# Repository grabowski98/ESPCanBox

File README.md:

<!-- Project name: "project_name" in project.json. tools/set_project_name.py --apply rewrites the title line ("# ...") under the logo. The logo is a drawing: no tool rewrites it (docs/en/contributing/brand.md). -->

# ESPCanBox

An open ESP32-S3 device that sits between a car's CAN bus and an Android radio and can replace
the aftermarket CAN interface box sold with the radio.

English | [Polski](README.pl.md) | [Deutsch](README.de.md) | [Español](README.es.md) | [Русский](README.ru.md) | [Українська](README.uk.md)

> [!WARNING]
> **Hobby project, provided AS IS, without any warranty.** You use it at your own risk, on your
> own car.
>
> - By default the device **only listens** to the car bus. Transmitting needs a separate build
>   (`decoder_tx_wifi`) and arming by hand. Read [Transmitting on the CAN bus](docs/en/safety/transmit.md)
>   before you build it.
> - Do not use it for anything that affects safety (brakes, steering, airbags, lights required by
>   law). It is not designed or tested for that.
> - The firmware and the board were developed and measured on **one** car with **one** radio.
>   Every other car is untested.
> - This project is not affiliated with, endorsed by or connected to Peugeot, Stellantis,
>   Simple Soft, Raise, Junsun or FYT. Their names are used only to say what was tested.

## Who it is for

Hobbyists who can solder a small board, use a multimeter and build firmware with PlatformIO
(the guides show every command). What you get depends on your car and radio:

- **Peugeot 508 SW (PSA AEE2010) with an Android radio that speaks the "XP" protocol:** the
  device can replace the CAN box: buttons, parking sensors, trip computer and radio power.
- **Any other car:** listen and record the CAN bus (build `listen_generic_wifi`), then decode it
  and write your own car profile with the [Make it yours](docs/en/make-it-yours/porting-checklist.md)
  guides. Nothing is sent to the radio until your profile exists.
- **Any other radio:** "XP" is the only radio protocol so far. Another radio needs a new
  protocol in the firmware ([Radio mapping](docs/en/make-it-yours/radio-mapping.md)).

## What it does

- **Listens to the car's CAN bus** and never transmits in the default builds. Only the separate
  build `decoder_tx_wifi` contains transmit code; a script checks this after every build.
- **Beeps for the parking sensors** from its own small speaker.
- **Talks to the radio** in decoder mode, like the CAN box did: steering wheel and centre panel
  buttons, parking sensor display, trip computer, outside temperature, climate state, doors and
  vehicle settings.
- **Switches three 12 V lines** for the radio in decoder mode: ACC (radio power), illumination,
  reverse.
- **Web panel** over its own Wi-Fi network: status, live CAN frames, console, recording,
  firmware update. Panel languages: English, Polish, German, Spanish, Russian, Ukrainian (the
  last four are machine translations that need review).
- **USB console** with a fixed line format that tools can read
  (see [Console](docs/en/reference/console.md)).
- **Car profiles and radio protocols chosen at build time:** `psa_aee2010` (reference car) or
  `generic` (any car, listen only); radio protocol `XP` or `NONE`. A template for your own car is
  in `firmware/lib/car_example` (see [Write a profile](docs/en/make-it-yours/write-a-profile.md)).
- **Tests on your computer** of all the logic, on recordings from the car, without hardware
  (see [Host tests](docs/en/testing/host-tests.md)).
- **Optional transmit build** (`decoder_tx_wifi`): by default it can send only one frame, the
  vehicle settings request `15B` (checked by ID and length only), and only after you arm it.
  Two more trial frames exist only in an experimental build. Climate control from the radio
  this way did **not** work. Details: [Transmitting on the CAN bus](docs/en/safety/transmit.md).

Not done or not known: deep sleep when the bus is silent is written but not tested on the
hardware. The firmware in this repository was reorganised from the version that runs in the
reference car; it compiles and passes the host tests, but this tree has **not yet been
bench-tested** on a device.

## Supported cars

| Car | Firmware profile | Status |
|---|---|---|
| Peugeot 508 SW, 2015 (PSA AEE2010) | `psa_aee2010` | measured on one car |
| any car | `generic` (build `listen_generic_wifi`) | listen-only: records frames, sends nothing to the radio, 12 V outputs off |

On the reference car the bus at the radio runs at 125 kbit/s (measured). Its voltages look like
low-speed fault-tolerant CAN (CANH about 0.65 V, CANL about 4.5 V average with ignition on); this
is not yet confirmed with an oscilloscope. Details: `vehicles/peugeot-508-sw-2015/README.md` and
`vehicles/SUPPORTED.md`.

## Supported radios

| Radio protocol | Firmware | Status |
|---|---|---|
| "XP" (Simple Soft CAN box protocol, Android radio on the FYT platform, CAN profile "XP Simple Soft -> Peugeot 508 -> Type 2") | `-DRADIO_PROTOCOL=XP` | measured on one radio (UART recordings of the box and the radio) |
| no radio | `-DRADIO_PROTOCOL=NONE` | nothing is sent on the UART |

Protocol description, only from recordings: `radios/xp-simple-soft/protocol.md`.

## Quick start

This gets the device running on your desk, with no car. You need an ESP32-S3 board with 16 MB
flash and 8 MB PSRAM (N16R8) and a USB cable. Full guide: [Quick start](docs/en/quick-start/flash.md).

1. **Read [Safety](docs/en/getting-started/safety.md).** Nothing goes into the car before that.
2. **Install the tools.** Install [uv](https://docs.astral.sh/uv/); it runs PlatformIO without a
   separate install. Git for Windows (Git Bash) is not needed to flash: it is needed for the
   tests on your computer and for the pages of "Make it yours" (your own car or radio).
3. **Build and flash the listen-only build with the web panel.** Type this in the top folder of
   the repository (on Windows in PowerShell):

   ```
   uvx platformio run -d firmware -e listen_wifi -t upload
   ```

4. **Open the USB console** (115200 baud), for example
   `uvx platformio device monitor -d firmware`. Your typing is not shown; press Enter after each
   command. Type `ver`, then `stat`, then `wifi` (network name) and `wifi showpass` (password).
   Keep the password out of any log you share.
5. **Open the panel.** Connect a phone or a laptop to the Wi-Fi network of the device (its name
   is printed by `wifi`), open `http://10.50.8.1` and log in with that password. Pick your
   language on the login screen.

For a car other than the reference car, use `listen_generic_wifi` later.

Next: [Bench test](docs/en/quick-start/bench-test.md), then
[Make it yours](docs/en/make-it-yours/porting-checklist.md) for another car, or
[Install in the car](docs/en/install-in-car/checklist.md) for the reference car.

No board yet? The mock device runs the panel on your computer with a recording:
`python -I firmware/tools/mock_device.py firmware/test_data/captures/can_20261111_191045.log`
(on Linux and macOS: `python3`; see [First boot](docs/en/quick-start/first-boot.md)).

## Documentation

- [Overview](docs/en/index.md) and [How it works](docs/en/getting-started/how-it-works.md)
- [Safety](docs/en/getting-started/safety.md), [Transmitting on the CAN bus](docs/en/safety/transmit.md),
  [Security model](docs/en/safety/security.md)
- [Hardware](docs/en/hardware/overview.md): prototype board, parts list, enclosure, wiring
- [Make it yours](docs/en/make-it-yours/porting-checklist.md): record, decode and add your own car
- [Reference](docs/en/reference/architecture.md): protocol, console, panel API, pins
- [Troubleshooting](docs/en/troubleshooting/index.md) and [FAQ](docs/en/troubleshooting/faq.md)

The documentation reads best as the built site: menu, search, language switcher. To see it on your
computer, run this in the top folder of the repository and open http://127.0.0.1:8000:

```
uvx --from mkdocs-material==9.8.1 --with mkdocs-static-i18n==1.3.1 mkdocs serve
```

The address of the site online will be added here after publication. The files in `docs/` can also
be read directly on GitHub; every link between them works there too.

## Languages

- Documentation: English (`docs/en/`, binding). Machine translations, not yet reviewed:
  [Polski](docs/pl/index.md) (every page), [Deutsch](docs/de/index.md), [Español](docs/es/index.md),
  [Русский](docs/ru/index.md), [Українська](docs/uk/index.md) (13 pages each); a missing page
  falls back to English. How to help: [Translations](docs/en/contributing/translations.md).
- Web panel: en, pl, de, es, ru, uk in `firmware/web/i18n/`.
- USB console, console commands and API codes: English only, on purpose (tools read them).

## Contributing

See [CONTRIBUTING.md](CONTRIBUTING.md), [CODE_OF_CONDUCT.md](CODE_OF_CONDUCT.md) and
[ROADMAP.md](ROADMAP.md). Security problems: [SECURITY.md](SECURITY.md). Changes:
[CHANGELOG.md](CHANGELOG.md).

This is a hobby project. Questions and pull requests are welcome, but there is no promise of an
answer or a fix within any time.

## Licences

Provisional until the first public release:

- code: Apache-2.0 ([LICENSE](LICENSE), [NOTICE](NOTICE));
- documentation and images: CC BY 4.0 ([LICENSE-docs](LICENSE-docs));
- hardware (KiCad files, enclosure): CERN-OHL-S-2.0 ([LICENSE-hardware](LICENSE-hardware)).

Author: grabowski98.

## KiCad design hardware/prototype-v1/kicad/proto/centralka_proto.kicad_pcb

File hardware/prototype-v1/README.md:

# Prototype v1: double-sided board for home etching

A carrier board for ready-made modules: ESP32-S3 dev board, CAN transceiver module, I2S
amplifier module, plus the 12 V input, the UART to the radio and three switched 12 V outputs.
Read [STATUS.md](STATUS.md) first: it says what is verified and how the transmit path is wired.

Board 100 x 77 mm. Tracks 0.8 mm, clearance 0.4 mm. **7 wire vias**: 5 join the bottom ground
with the top ground, 2 are the ends of one 5 V jumper on the top side.

## Files

| File | Content |
|---|---|
| `kicad/` | schematic (KiCad 10), symbol library `centralka.kicad_sym` |
| `kicad/proto/centralka_proto.kicad_pcb` | PCB with tracks and ground fill |
| `pdf/schematic.pdf` | schematic, all sheets |
| `print/1_bottom_copper_toner_transfer.pdf` | bottom copper, **not mirrored** |
| `print/2_top_copper_mirrored_toner_transfer.pdf` | top copper, **mirrored** |
| `print/3_assembly_top_view.pdf`, `4_assembly_bottom_view.pdf` | part placement for drilling and soldering (2:1) |
| `images/assembly_map_bottom_view.png` | what to solder where, polarity (red pad), seen from the solder side |
| `images/drill_map_bottom_view.png` | holes coloured by drill size, seen from the solder side |
| `images/esp32_socket_test_map_bottom_view.png` | multimeter checks of the ESP32 sockets before inserting the modules |
| `images/ground_wire_vias.png` | where the ground wire vias go |
| `images/preview_*`, `images/render_*` | previews and 3D renders |
| `bom.csv` | parts list |
| `enclosure/` | 3D-printed enclosure |

The KiCad file, sheet and library names (`centralka*`) are the working name of the prototype, from
before the project was named. They are kept so the project files keep their links.

### Legends of the images (they are in Polish)

- `assembly_map_bottom_view.png`: "MONTAZ - WIDOK ZE SPODU" = assembly, bottom view (track side,
  J5 top right). Colours: yellow resistors 0805, blue capacitors (T = tantalum), pink diodes
  SMA/SMB, green PTC fuses 1812, violet SOT-23 transistors. **Red pad** = diode cathode (band),
  tantalum/electrolytic plus, transistor pin 1. Grey = part inserted from the top, soldered on the
  bottom only. Blue ring = wire via (7). Green frame: Q2, Q4, Q6 = AO3407 (marking "3407").
  Transistor pins: BC847 1 B, 2 E, 3 C; AO3407 1 G, 2 S, 3 D. Order: 1. resistors and 0805
  capacitors, 2. transistors, diodes, PTC, tantalums, 3. electrolytics C1, C4 (tall), 4. the 7
  wire vias, 5. TRACO, J5, Zener diodes, 6. sockets; JP1 stays empty. "(gora)" = part on the top.
- `drill_map_bottom_view.png`: "Wiertla" = drills: 0.8 mm x13 (wire vias, Zener diodes), 1.0 mm
  x63 (sockets, TRACO, JP1), 1.2 mm x5 (J4 wires), 1.3 mm x4 (J5 terminals), 3.2 mm x3 (M3 holes).
  Bottom view, the side you drill from.
- `esp32_socket_test_map_bottom_view.png`: multimeter checks of the empty sockets, solder side.
  Black GND (M1 pin 22, M2 pins 1, 21, 22), orange +3V3 (M1 pins 1, 2 -> VCC of the CAN module),
  red +5V (M1 pin 21 -> plus of C4), blue dashed = signal to its destination, white = unused pin.
  1. Continuity tester, NO power: no neighbouring pins beep (except M1 1-2 and M2 21-22); black
     pins beep to GND of J5; coloured pins beep to the ring of their colour. Pins 7 and 11 have
     100k / 10k to GND: no beep is right (ohmmeter about 85k / 10k).
  2. 12 V, 100 mA limit, NO ESP32, meter minus on GND of J5: M1 pin 21 4.6-4.8 V; M1 pins 1, 2
     0 V (3.3 V comes from the ESP32 board); M1 pin 7 about 1.9-2.0 V; current a few mA.
  3. ESP32 in the sockets (USB on the pin 22 side): M1 pins 1, 2 and VCC of the CAN module 3.3 V;
     current tens of mA; if the supply hits the limit, switch off at once.
  4. CAN module (terminator OFF) and amplifier, then the firmware.
- `ground_wire_vias.png`: red = the 5 ground vias (wire, soldered on both sides); blue = the 5 V
  wire jumper. "RX radia (dolny 8)" = radio RX (harness lower 8), "TX radia (gorny 7)" = radio TX
  (harness upper 7).

## Connectors

- **J5, screw terminals 5.08 mm (2x KF301-2P), from the top:** CANH, CANL, GND, +12V. Power and
  CAN wires from the car harness (or a bench supply).
- **J4, wire pads** (1.2 mm hole, 3 mm pad), from the top: **radio RX, radio TX, ACC, ILL, REV.**
  "From the top" = from the J5 side. "Radio RX" is the line the board transmits on (the radio
  receives it). Swapping the two data wires = the radio neither receives nor answers.
- The 2x8 harness socket is not on the board (its dimensions were not measured). On the
  reference car a 2x8 socket desoldered from an old CAN box is wired to J5 / J4 with short leads.
  Pin map of that harness: [vehicles/peugeot-508-sw-2015/wiring.md](../../vehicles/peugeot-508-sw-2015/wiring.md).

Module pin order (check against the print on your module before etching):

- CAN Pal: from the bottom 1 CANL, 2 CANH, 3 SLNT, 4 TX, 5 RX, 6 GND, 7 VCC (3.3 V);
- MAX98357A: from the top 1 LRC, 2 BCLK, 3 DIN, 4 GAIN, 5 SD, 6 GND, 7 VIN (5 V).

Amplifier gain: GAIN input left open (module default). Speaker: screwed to the terminal of the
amplifier module. The amplifier output is bridged: neither speaker wire may touch ground.

## Making the board

1. Print sheets 1 and 2 at 100 % scale (no "fit to page"; the frame lets you check the scale
   with a ruler). Bottom **not mirrored**, top **mirrored**: the toner always faces the copper.
   **Check: the texts "SPOD v1" (bottom) and "GORA v1" (top) are mirrored on the paper and
   readable on the copper.** Assembly sheets 3 and 4 are at 2:1, only to look at.
2. Drill the three M3 holes first (top left next to J5, top right corner, bottom right corner) and
   align both sides on them. The top ground keeps 1 mm from every hole, so an offset of the top
   side up to about 1 mm does not short a socket pin.
3. After etching inspect with a magnifier. The smallest gap between copper of different nets is
   0.4 mm, in about 17 places. The bottom ground fill keeps 0.6 mm from the pads.
4. Drilling (hole centres are small dots): 0.8 mm x13 (7 vias, 3 Zener diodes), 1.0 mm x63
   (sockets, TRACO, JP1), 1.2 mm x5 (J4), 1.3 mm x4 (J5), 3.2 mm x3 (M3). Without a 0.8 mm drill
   use 1.0 mm (annular ring about 0.65 mm). **Do not drill the sockets larger than 1.0 mm**: along
   a row the ring is only 0.52 mm.
5. Soldering order: SMD parts on the bottom -> 7 wire vias (wire through the hole, solder both
   sides; two are 1.6 mm from the ESP32 header, so before the sockets) -> TRACO, terminals, Zener
   diodes -> sockets last.
6. **Through-hole pads are soldered on the bottom only.** The rings around the holes on the top
   side are dead copper.
7. The top ground joins the bottom only through the 5 ground wire vias. Without them parts of the
   bottom ground float (for example the ground of the converter, of the CAN module and of the
   output transistors).
8. The ground pins of the module sockets (M1-M4) join the fill with solid copper (no thermal
   relief): solder a little longer. The socket pads are 0.5 mm apart: check neighbouring pins for
   shorts after soldering.
9. C1 and C4 (SMD 8x10) are 10 mm tall and sit on the bottom: the board needs standoffs of at
   least 12 mm (the enclosure has them).

## First power-up (no modules)

1. Multimeter: no short +12V-GND, +5V-GND, +3V3-GND (pads near J5, C4, C6).
2. 12 V bench supply with current limit about 100 mA on J5 (terminal 4 = +12V, 3 = GND): about
   4.6-4.8 V on C4 (5 V through diode D3).
3. Only then the ESP32 board, then the modules.

## If a part is missing

- No 12 V Zener (D5, D7, D9): the board works without them; they only protect the MOSFET gates.
- No polymer fuses: a wire bridge in place of F1-F4 **on the bench only**, with a fuse in the +12 V
  lead of the supply.
- No SMBJ18A (D2): may be left out on the bench; **fit it before the car**.

## Before the car

- D2 fitted, C1 rated 35 V or more.
- JP1 open (listen-only hardware), unless you build the transmit firmware on purpose.
- No 120 ohm terminator anywhere: the car bus is terminated already. The CAN Pal terminator
  switch OFF.
- Check without power: no short between neighbouring socket pins and between +12 V and ground;
  CANH-CANL tens of kOhm.

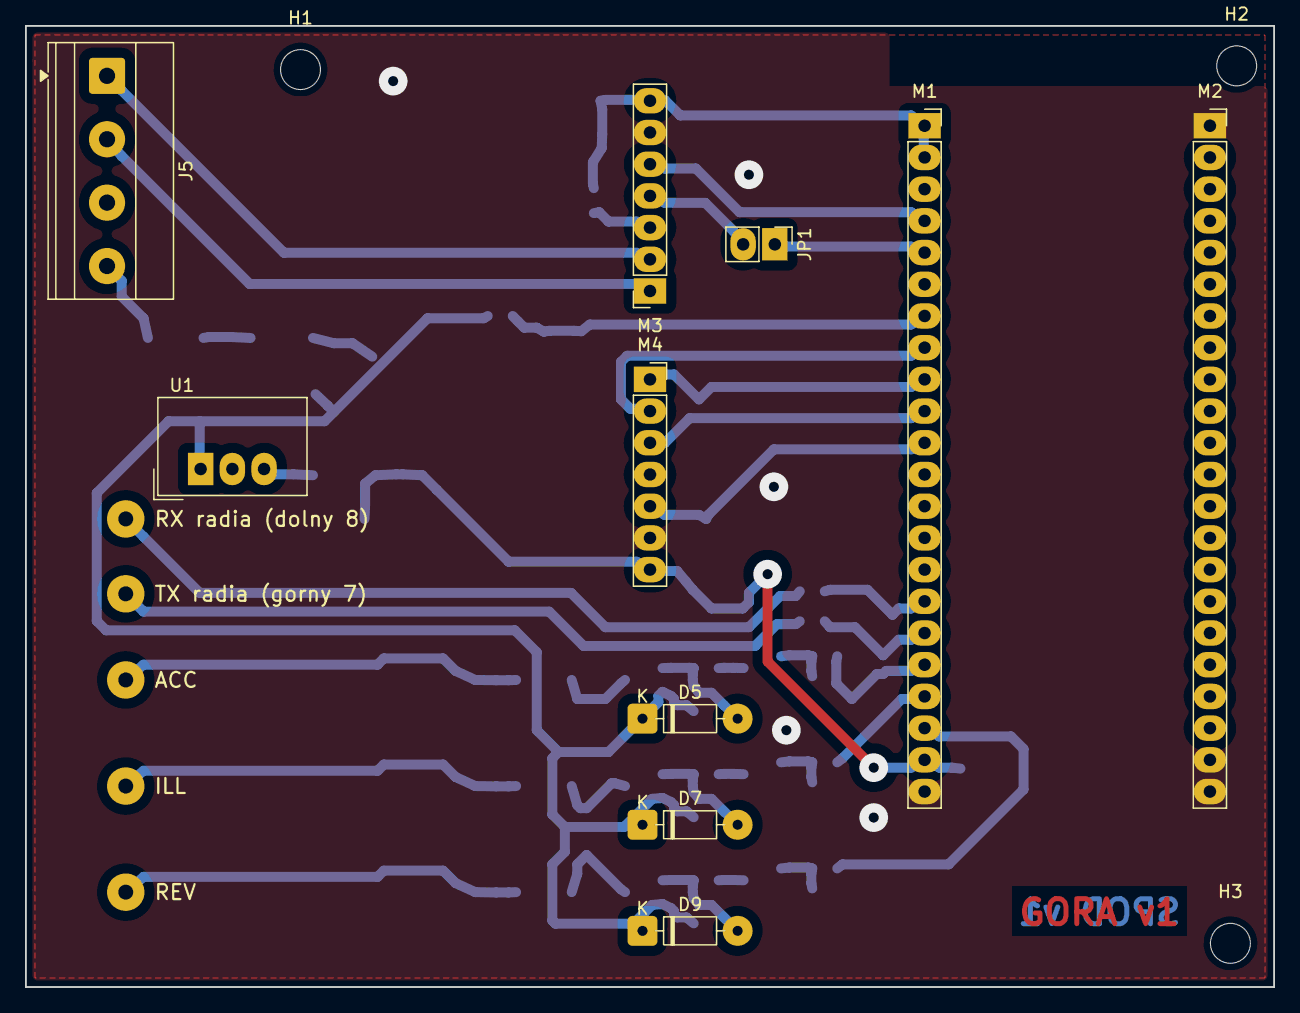
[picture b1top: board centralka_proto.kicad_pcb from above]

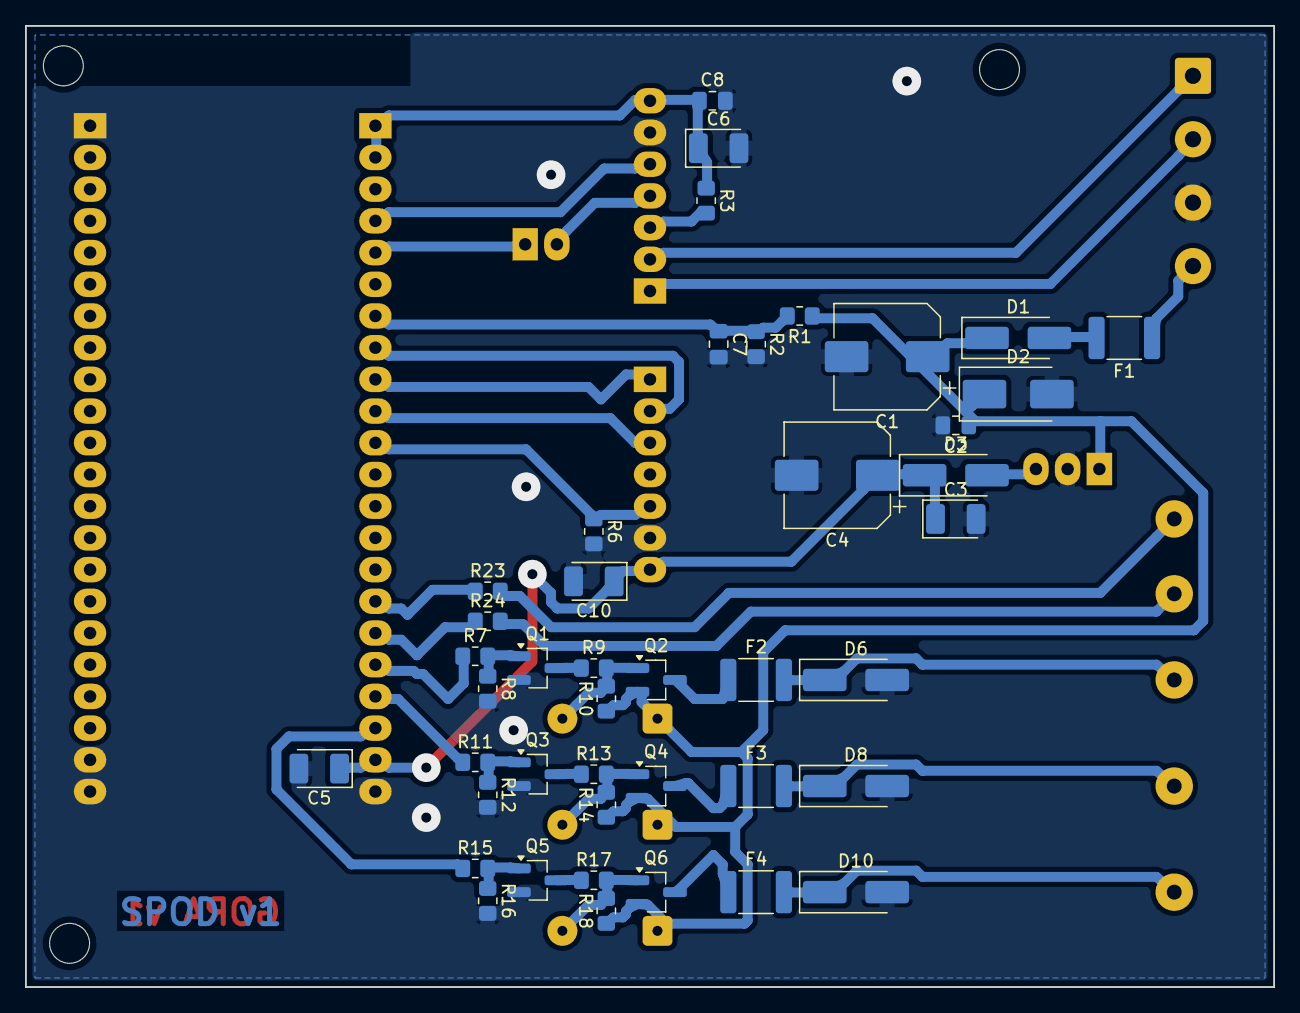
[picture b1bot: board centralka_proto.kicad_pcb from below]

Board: 2 copper layers, 100.0 x 77.0 mm, 57 parts (43 on the bottom side), 40 nets.

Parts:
C1: 100u/35V; CP_Elec_8x10
C2: 100n/50V; C_0805_2012Metric_Pad1.18x1.45mm_HandSolder
C3, C5, C6, C10: 10u tantal; CP_EIA-3528-21_Kemet-B_HandSolder
C4: 470u/16V; CP_Elec_8x10
C7, C8: 100n; C_0805_2012Metric_Pad1.18x1.45mm_HandSolder
D1, D3: SS34; D_SMA_Handsoldering
D2: SMBJ18A; D_SMB_Handsoldering
D5, D7, D9: Zener 12V; D_DO-35_SOD27_P7.62mm_Horizontal
D6, D8, D10: SS14; D_SMA_Handsoldering
F1: PTC 1,1A / 30V; Fuse_1812_4532Metric_Pad1.30x3.40mm_HandSolder
F2, F3, F4: PTC 0,5A / 30V; Fuse_1812_4532Metric_Pad1.30x3.40mm_HandSolder
H1, H2, H3: śruba M3; MountingHole_3.2mm_M3
J4: przewody z wiązki
J5: CANH CANL GND 12V; TerminalBlock_Phoenix_MKDS-1,5-4-5.08_1x04_P5.08mm_Horizont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
JP1: JP_TX; PinHeader_1x02_P2.54mm_Vertical
M1: ESP32-S3-DEV-KIT_lewy; PinSocket_1x22_P2.54mm_Vertical
M2: ESP32-S3-DEV-KIT_prawy; PinSocket_1x22_P2.54mm_Vertical
M3: CAN_Pal; PinSocket_1x07_P2.54mm_Vertical
M4: MAX98357A_modul; PinSocket_1x07_P2.54mm_Vertical
Q1, Q3, Q5: BC847A (1E); SOT-23_Handsoldering
Q2, Q4, Q6: AO3407 (A7); SOT-23_Handsoldering
R1: 470k; R_0805_2012Metric_Pad1.20x1.40mm_HandSolder
R2, R8, R12, R16: 100k; R_0805_2012Metric_Pad1.20x1.40mm_HandSolder
R3, R6, R10, R14, R18: 10k; R_0805_2012Metric_Pad1.20x1.40mm_HandSolder
R7, R9, R11, R13, R15, R17, R24: 4k7; R_0805_2012Metric_Pad1.20x1.40mm_HandSolder
R23: 1k; R_0805_2012Metric_Pad1.20x1.40mm_HandSolder
U1: TSR_1-2450; Converter_DCDC_TRACO_TSR-1_THT

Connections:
+3V3: C6.1, C8.1, M1.1, M1.2, M3.7, R3.1
+5V: C3.1, C4.1, C5.1, C10.1, D3.1, M1.21, M4.7
+12V: C1.1, C2.1, D1.1, D2.1, D5.1, D7.1, D9.1, Q2.2, Q4.2, Q6.2, R1.1, R10.1, R14.1, R18.1, U1.1
+12V_IN: F1.1, J5.4
ACC_EN: M1.18, R7.1
ACC_OUT: D6.1, F2.2, J4.5
AMP_SD: M1.11, M4.5, R6.1
CANH: J5.1, M3.2
CANL: J5.2, M3.1
CAN_RX: M1.4, M3.5
CAN_SLNT: M3.3, R3.2
CAN_TX: JP1.1, M1.5
CAN_TXD_M: JP1.2, M3.4
GND: C1.2, C2.2, C3.2, C4.2, C5.2, C6.2, C7.2, C8.2, C10.2, D2.2, D6.2, D8.2, D10.2, J5.3, M1.22, M2.1, M2.21, M2.22, M3.6, M4.6, Q1.2, Q3.2, Q5.2, R2.2, R6.2, R8.2, R12.2, R16.2, U1.2
I2S_BCLK: M1.8, M4.2
I2S_DIN: M1.10, M4.3
I2S_LRC: M1.9, M4.1
ILL_EN: M1.19, R11.1
ILL_OUT: D8.1, F3.2, J4.6
unnamed: D1.2, F1.2
unnamed: D3.2, U1.3
unnamed: D5.2, Q2.1, R9.2, R10.2
unnamed: D7.2, Q4.1, R13.2, R14.2
unnamed: D9.2, Q6.1, R17.2, R18.2
unnamed: Q1.1, R7.2, R8.1
unnamed: Q1.3, R9.1
unnamed: F2.1, Q2.3
unnamed: Q3.1, R11.2, R12.1
unnamed: Q3.3, R13.1
unnamed: F3.1, Q4.3
unnamed: Q5.1, R15.2, R16.1
unnamed: Q5.3, R17.1
unnamed: F4.1, Q6.3
RADIO_A: J4.14, R24.2
RADIO_B: J4.15, R23.2
REV_EN: M1.20, R15.1
REV_OUT: D10.1, F4.2, J4.7
UART_RX: M1.17, R24.1
UART_TX: M1.16, R23.1
VBAT_SENSE: C7.1, M1.7, R1.2, R2.1

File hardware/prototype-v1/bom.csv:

references,qty,value,footprint,typical part,function,notes
M1 M2,2,ESP32-S3 dev board (2x 1x22 socket),PinSocket_1x22_P2.54mm_Vertical,"ESP32-S3 dev board with ESP32-S3-WROOM-1-N16R8, row spacing 22.86 mm (Waveshare ESP32-S3-DEV-KIT-N16R8 used)",processor,plugged into two 1x22 female headers; the board's own 3.3 V regulator supplies the CAN module
M3,1,CAN transceiver module (1x7 socket),PinSocket_1x07_P2.54mm_Vertical,Adafruit CAN Pal (TJA1051T/3),CAN transceiver,pin order from the bottom: 1 CANL 2 CANH 3 SLNT 4 TX 5 RX 6 GND 7 VCC (3.3 V); terminator switch OFF
M4,1,I2S amplifier module (1x7 socket),PinSocket_1x07_P2.54mm_Vertical,MAX98357A module,sound (parking tone),pin order from the top: 1 LRC 2 BCLK 3 DIN 4 GAIN 5 SD 6 GND 7 VIN (5 V); speaker 4-8 ohm 2-3 W on the module terminal
U1,1,TSR 1-2450,Converter_DCDC_TRACO_TSR-1_THT,Traco TSR 1-2450 (6.5-36 V in / 5 V 1 A out),12 V to 5 V,any 5 V / 1 A switching module with the 7805 pinout should fit (not tested)
F1,1,PTC 1.1 A / 30 V,Fuse_1812_4532Metric,polymer resettable fuse 1812,input fuse,min. 30 V rating
F2 F3 F4,3,PTC 0.5 A / 30 V,Fuse_1812_4532Metric,polymer resettable fuse 1812,fuses of the 12 V outputs,min. 30 V rating
D1 D3,2,SS34,D_SMA,SS34 (alternatives SS36 / B340A / SS24),D1 reverse polarity; D3 separates the converter from USB 5 V,
D2,1,SMBJ18A,D_SMB,SMBJ18A (alternative SMAJ18A / P6SMB18A),input surge clamp (after F1),mandatory before connecting to a car; cathode band to +12 V
D5 D7 D9,3,Zener 12 V,D_DO-35_P7.62mm,"12 V 0.5 W Zener, through hole (BZX85C12 in DO-41 fits after drilling 1.0 mm)",gate protection of Q2/Q4/Q6,optional on the bench; recommended in the car; cathode to +12 V
D6 D8 D10,3,SS14,D_SMA,SS14 / SS24 / 1N4148W,output clamp diodes,
Q1 Q3 Q5,3,BC847A,SOT-23,BC847 / BC817 / MMBT3904,output drivers (NPN),
Q2 Q4 Q6,3,AO3407,SOT-23,AO3407A (-30 V; gate +/-20 V),high-side switches ACC / ILL / REV (P-MOSFET),not AO3401A (gate only +/-12 V)
C1,1,100 uF / 35 V,CP_Elec_8x10,"electrolytic, low ESR, 105 C, 8x10 mm",input reservoir,min. 35 V in the car; 10 mm tall: the board needs 12 mm standoffs
C2,1,100 nF / 50 V,C_0805,ceramic X7R,input decoupling,min. 25 V
C3 C5 C6 C10,4,10 uF,CP_EIA-3528-21,tantalum 10 uF 10 V (or ceramic),decoupling 5 V / 3.3 V,
C4,1,470 uF / 16 V,CP_Elec_8x10,"electrolytic, 8x10 mm",5 V reservoir (amplifier peaks and Wi-Fi),
C7 C8,2,100 nF,C_0805,ceramic,decoupling / ADC filter,
R1,1,470k,R_0805,,battery voltage divider (top),470k / 100k: 16 V -> 2.8 V
R2,1,100k,R_0805,,battery voltage divider (bottom),
R3,1,10k,R_0805,,SLNT pull-up to 3.3 V,keeps the CAN module silent after reset
R6 R10 R14 R18,4,10k,R_0805,,gate-source resistors / pull-ups,
R7 R9 R11 R13 R15 R17,6,4k7,R_0805,,base and collector resistors of the output stages,
R8 R12 R16,3,100k,R_0805,,base pull-downs (outputs off after reset),
R23,1,1k,R_0805,,UART transmit line to the radio,
R24,1,4k7,R_0805,,UART receive line from the radio,safe with a 5 V level
J5,1,4-way screw terminal 5.08 mm,TerminalBlock_1x04_P5.08mm,2x KF301-2P side by side,"CANH, CANL, GND, +12V (from the top)",
J4,1,5 wire pads (no part),-,,"wires to the radio harness: radio RX, radio TX, ACC, ILL, REV (from the top)",1.2 mm holes; a 2x8 socket from an old CAN box is wired with short leads
JP1,1,2-pin jumper,PinHeader_1x02_P2.54mm,wire bridge or header,TX line to the CAN module,leave OPEN for a listen-only build (see STATUS.md)
H1 H2 H3,3,M3 holes,MountingHole_3.2mm_M3,M3 x 6-8 mm screws,mounting,

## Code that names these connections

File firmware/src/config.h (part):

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#include "board_common.h"         // pin rules (no 35-37, 19/20; strapping pins only with a reason)

// ---------- CAN (transceiver pins: board header) ----------
const gpio_num_t PIN_CAN_RX = BOARD_PIN_CAN_RX;
const gpio_num_t PIN_CAN_TX = BOARD_PIN_CAN_TX;
// Transceiver silent pin: HIGH = transmitter off. In the five environments without transmission, and in the
// transmitting program as long as it is not armed, it is permanently high and TWAI is in listen-only mode.
// The LOW level is set only by src/can_tx/can_tx_port.cpp (environment decoder_tx_wifi), for one frame.
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#endif

// ---------- Sound (MAX98357A module, I2S; pins: board header) ----------
const int PIN_I2S_BCLK = BOARD_PIN_I2S_BCLK;
const int PIN_I2S_LRC = BOARD_PIN_I2S_LRC;
const int PIN_I2S_DIN = BOARD_PIN_I2S_DIN;
// Amplifier SD: low = amplifier off (pull-down on the board: silence before the program starts).
const int PIN_AMP_SD = BOARD_PIN_AMP_SD;
const int AUDIO_SAMPLE_RATE = 22050;        // Hz
const int AUDIO_VOLUME_DEFAULT = 40;        // percent of full scale
// Upper volume limit. Speaker from the Simple Soft kit: 8 Ω / 0.5 W, i.e. 2.0 V RMS.
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// ---------- Other ----------
const int PIN_I2C_SDA = BOARD_PIN_I2C_SDA;
const int PIN_I2C_SCL = BOARD_PIN_I2C_SCL;
const int PIN_VBAT_SENSE = BOARD_PIN_VBAT_SENSE;  // divider from the 12 V rail
const float VBAT_DIVIDER = (BOARD_VBAT_R_TOP_K + BOARD_VBAT_R_BOTTOM_K) / BOARD_VBAT_R_BOTTOM_K;
// 0 = no divider on the board. The measurement shows the voltage behind the input diode; without 12 V
// (powered from USB) it shows noise; below NET_VBAT_VALID_MIN_V the console and the panel assume there is no 12 V.
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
